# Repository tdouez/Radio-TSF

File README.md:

# Radio FM TSF

  Radio FM avec l'utilisation d'un arduino nano, récepteur TEA5767 et le condensateur variable existant de la radio TSF.

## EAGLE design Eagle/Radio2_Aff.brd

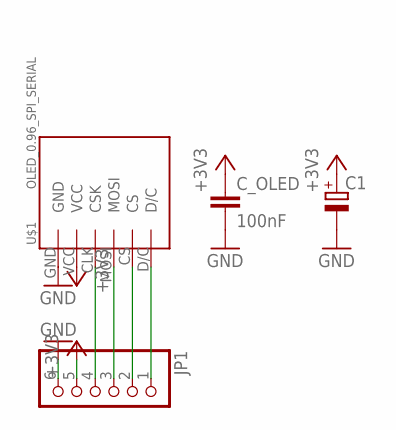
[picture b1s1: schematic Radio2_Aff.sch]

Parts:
C1: CPOL-EUE2-5; E2-5
C_OLED: 100nF; C025-024X044
JP1: PINHD-1X6; 1X06
U$1: OLED_0.96_SPI_SERIAL; OLED_9.96_SPI_SERIAL

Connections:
+3V3: C1.+, C_OLED.1, JP1.5, U$1.VCC
GND: C1.-, C_OLED.2, JP1.6, U$1.GND
unnamed: JP1.1, U$1.D/C
unnamed: JP1.2, U$1.CS
unnamed: JP1.3, U$1.MOSI
unnamed: JP1.4, U$1.CLK (CSK)

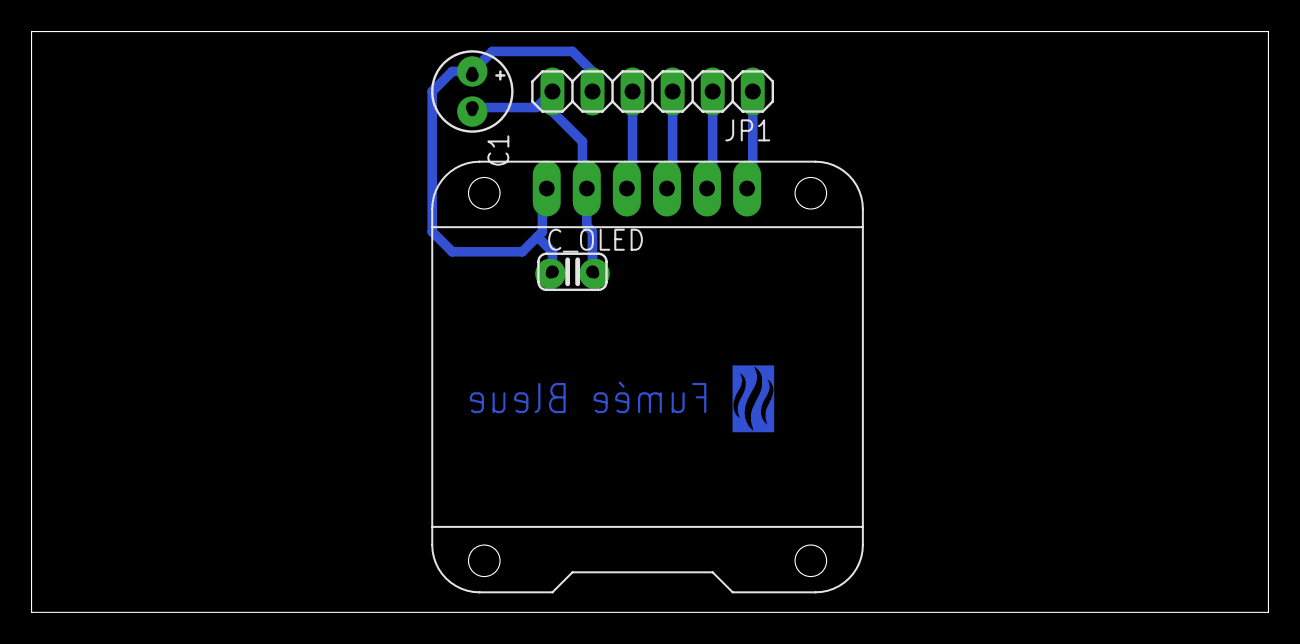
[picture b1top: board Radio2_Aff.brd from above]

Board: 2 copper layers, 78.4 x 36.8 mm, 5 parts (0 on the bottom side), 6 nets.

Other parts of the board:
U$2: FB

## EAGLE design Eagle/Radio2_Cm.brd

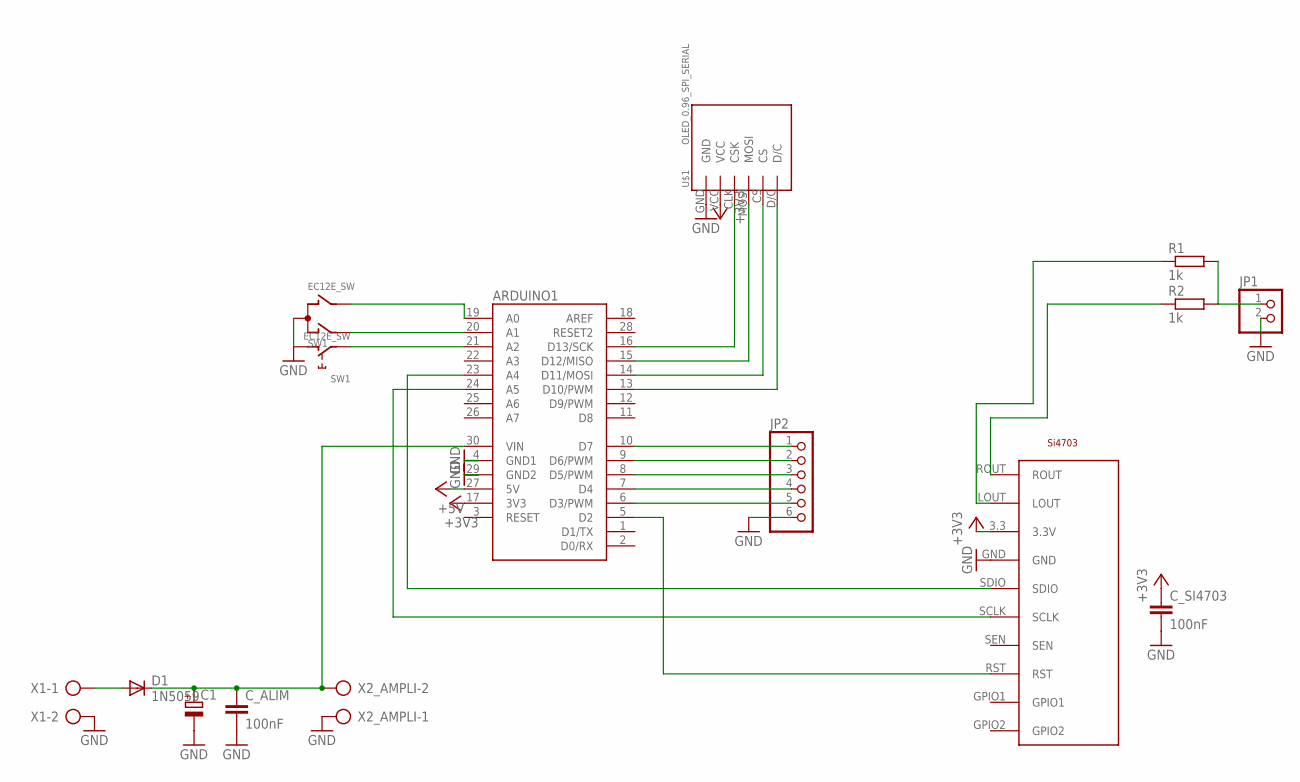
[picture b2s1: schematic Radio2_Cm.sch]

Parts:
ARDUINO1: ARDUINO_NANO
C1: CPOL-EUE7.5-16; E7,5-16
C_ALIM: 100nF; C025-024X044
C_SI4703: 100nF; C025-024X044
D1: 1N5059; DO204-10
JP1: PINHD-1X2; 1X02
JP2: PINHD-1X6; 1X06
R1, R2: 1k; 0207/10
SW1: EC12E_SW; ALPS_EC12E_SW
U$1: OLED_0.96_SPI_SERIAL; OLED_9.96_SPI_SERIAL
U$3: SI4703
X1, X2_AMPLI: AK300/2

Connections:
+3V3: ARDUINO1.17 (3V3), C_SI4703.1, U$1.VCC, U$3.3.3 (3.3V)
+5V: ARDUINO1.27 (5V)
GND: ARDUINO1.4 (GND1), ARDUINO1.29 (GND2), C1.-, C_ALIM.2, C_SI4703.2, JP1.2, JP2.6, SW1.C, SW1.D (1), U$1.GND, U$3.GND, X1.2, X2_AMPLI.1
unnamed: ARDUINO1.16 (D13/SCK), U$1.CLK (CSK)
unnamed: ARDUINO1.5 (D2), U$3.RST
unnamed: ARDUINO1.6 (D3/PWM), JP2.5
unnamed: ARDUINO1.7 (D4), JP2.4
unnamed: ARDUINO1.8 (D5/PWM), JP2.3
unnamed: ARDUINO1.9 (D6/PWM), JP2.2
unnamed: ARDUINO1.15 (D12/MISO), U$1.MOSI
unnamed: ARDUINO1.14 (D11/MOSI), U$1.CS
unnamed: ARDUINO1.10 (D7), JP2.1
unnamed: ARDUINO1.23 (A4), U$3.SDIO
unnamed: D1.A, X1.1
unnamed: ARDUINO1.30 (VIN), C1.+, C_ALIM.1, D1.C, X2_AMPLI.2
unnamed: R2.1, U$3.ROUT
unnamed: R1.1, U$3.LOUT
unnamed: JP1.1, R1.2, R2.2
unnamed: ARDUINO1.13 (D10/PWM), U$1.D/C
unnamed: ARDUINO1.21 (A2), SW1.E (2)
unnamed: ARDUINO1.20 (A1), SW1.A
unnamed: ARDUINO1.19 (A0), SW1.B
unnamed: ARDUINO1.24 (A5), U$3.SCLK
RESET2: ARDUINO1.28 (RESET2)

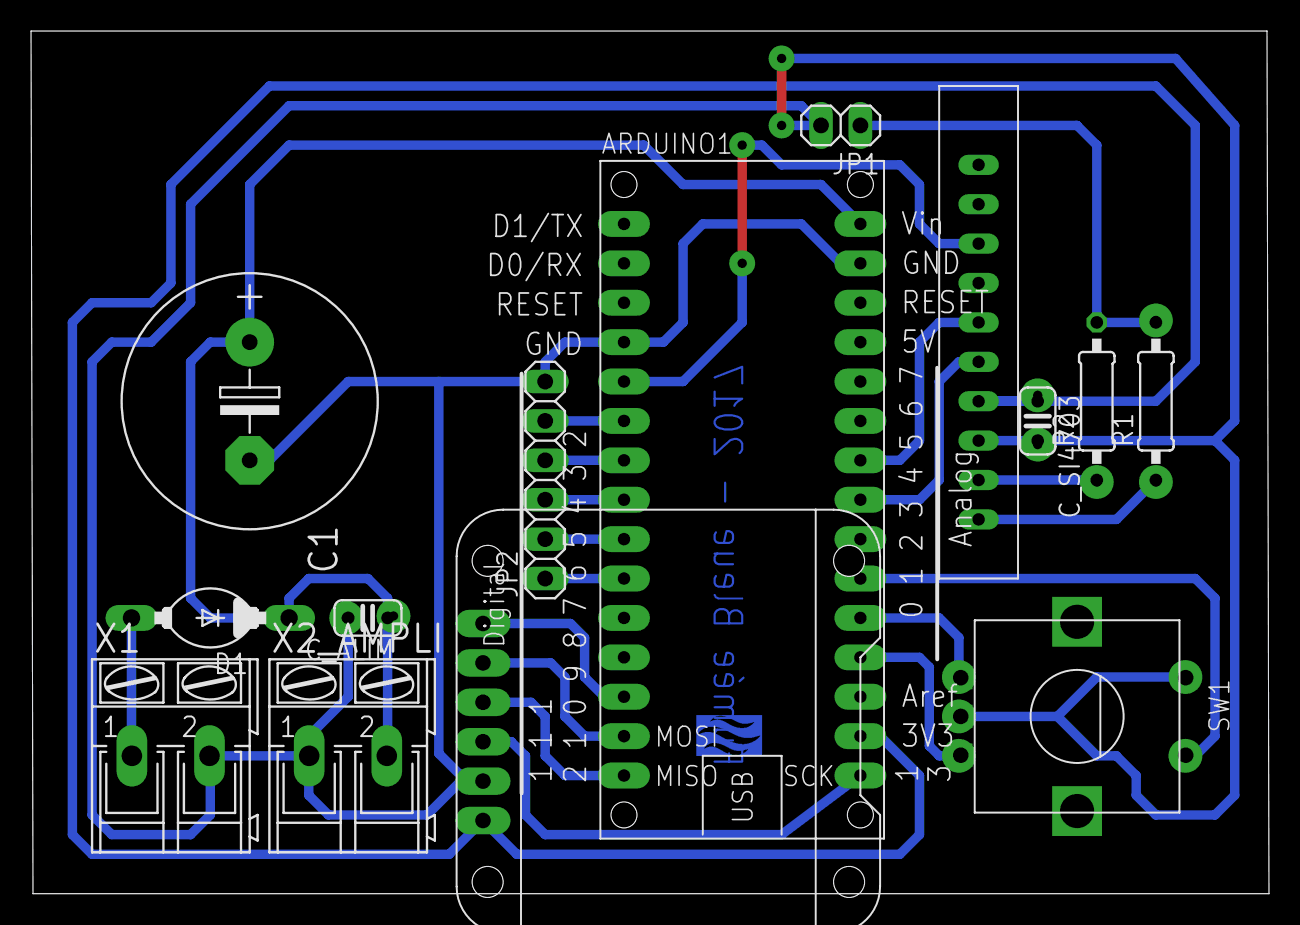
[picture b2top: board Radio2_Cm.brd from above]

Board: 2 copper layers, 79.8 x 55.6 mm, 15 parts (0 on the bottom side), 22 nets.

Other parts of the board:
U$2: FB

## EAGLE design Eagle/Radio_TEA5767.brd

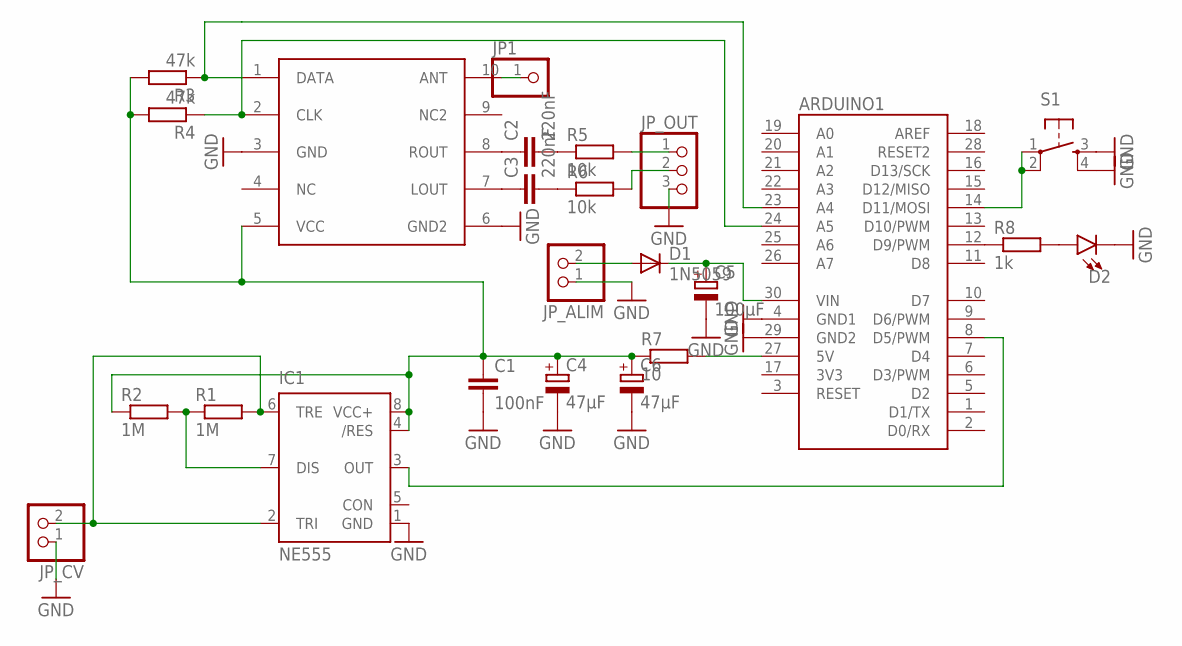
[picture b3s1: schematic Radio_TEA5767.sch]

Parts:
ARDUINO1: ARDUINO_NANO
C1: 100nF; C025-025X050
C2, C3: 220nF; C050-030X075
C4, C6: 47μF; E2,5-7
C5: 100μF; E2,5-7
D1: 1N5059; DO204-10
D2: LED3MM; LED_3MM
IC1: NE555; DIL-08
JP1: PINHD-1X1; 1X01
JP_ALIM: PINHD-1X2; 1X02
JP_CV: PINHD-1X2; 1X02
JP_OUT: PINHD-1X3; 1X03
R1, R2: 1M; 0207/10
R3, R4: 47k; 0207/10
R5, R6: 10k; 0207/10
R7: 10; 0207/10
R8: 1k; 0207/10
S1: TAC_SWITCHPTH; TACTILE-PTH
U$1: TEA5767; RDA

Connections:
3V3: ARDUINO1.17 (3V3)
GND: ARDUINO1.4 (GND1), ARDUINO1.29 (GND2), C1.2, C4.-, C5.-, C6.-, D2.K (C), IC1.1 (GND), JP_ALIM.1, JP_CV.1, JP_OUT.3, S1.3, S1.4, U$1.3 (GND), U$1.6 (GND2)
unnamed: IC1.2 (TRI), IC1.6 (TRE), JP_CV.2, R1.2
unnamed: IC1.7 (DIS), R1.1, R2.2
unnamed: C2.1, U$1.8 (ROUT)
unnamed: JP1.1, U$1.10 (ANT)
unnamed: ARDUINO1.30 (VIN), C5.+, D1.C
unnamed: ARDUINO1.24 (A5), R4.1, U$1.2 (CLK)
unnamed: C1.1, C4.+, C6.+, IC1.4 (/RES), IC1.8 (VCC+), R2.1, R3.2, R4.2, R7.1, U$1.5 (VCC)
unnamed: C2.2, R5.1
unnamed: JP_OUT.1, R5.2
unnamed: JP_OUT.2, R6.2
unnamed: C3.1, U$1.7 (LOUT)
unnamed: C3.2, R6.1
unnamed: ARDUINO1.23 (A4), R3.1, U$1.1 (DATA)
unnamed: ARDUINO1.12 (D9/PWM), R8.1
unnamed: ARDUINO1.14 (D11/MOSI), S1.1, S1.2
unnamed: ARDUINO1.27 (5V), R7.2
unnamed: D2.A, R8.2
unnamed: ARDUINO1.8 (D5/PWM), IC1.3 (OUT)
unnamed: D1.A, JP_ALIM.2
RESET2: ARDUINO1.28 (RESET2)

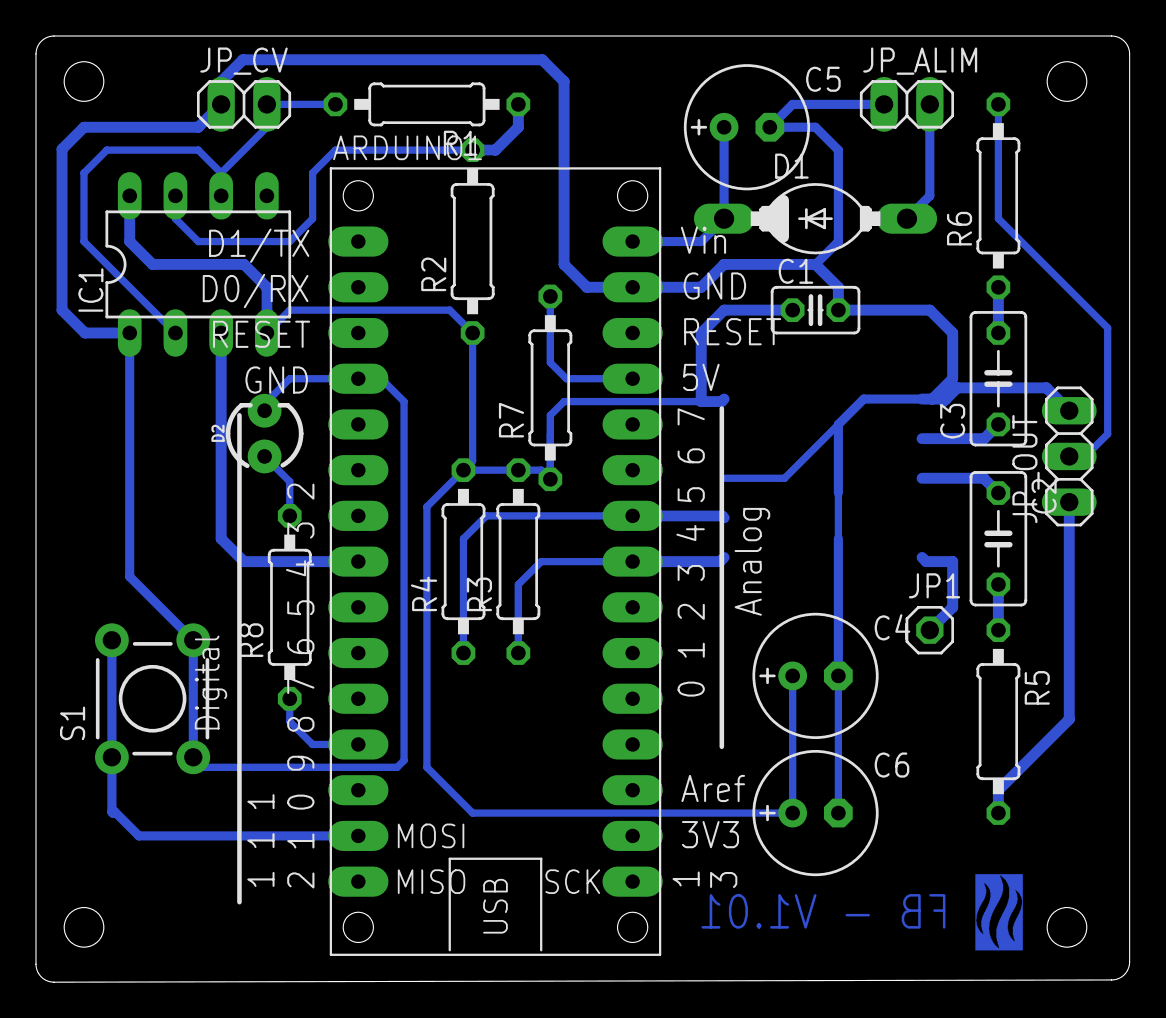
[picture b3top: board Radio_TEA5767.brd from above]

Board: 2 copper layers, 60.8 x 52.6 mm, 25 parts (1 on the bottom side), 20 nets.

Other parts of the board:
U$2: FB

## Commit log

2022-11-06 V1.0.0

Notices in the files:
parts and their libraries:
SparkFun-Retired: Licensing: Creative Commons ShareAlike 4.0 International - https://creativecommons.org/licenses/by-sa/4.0
